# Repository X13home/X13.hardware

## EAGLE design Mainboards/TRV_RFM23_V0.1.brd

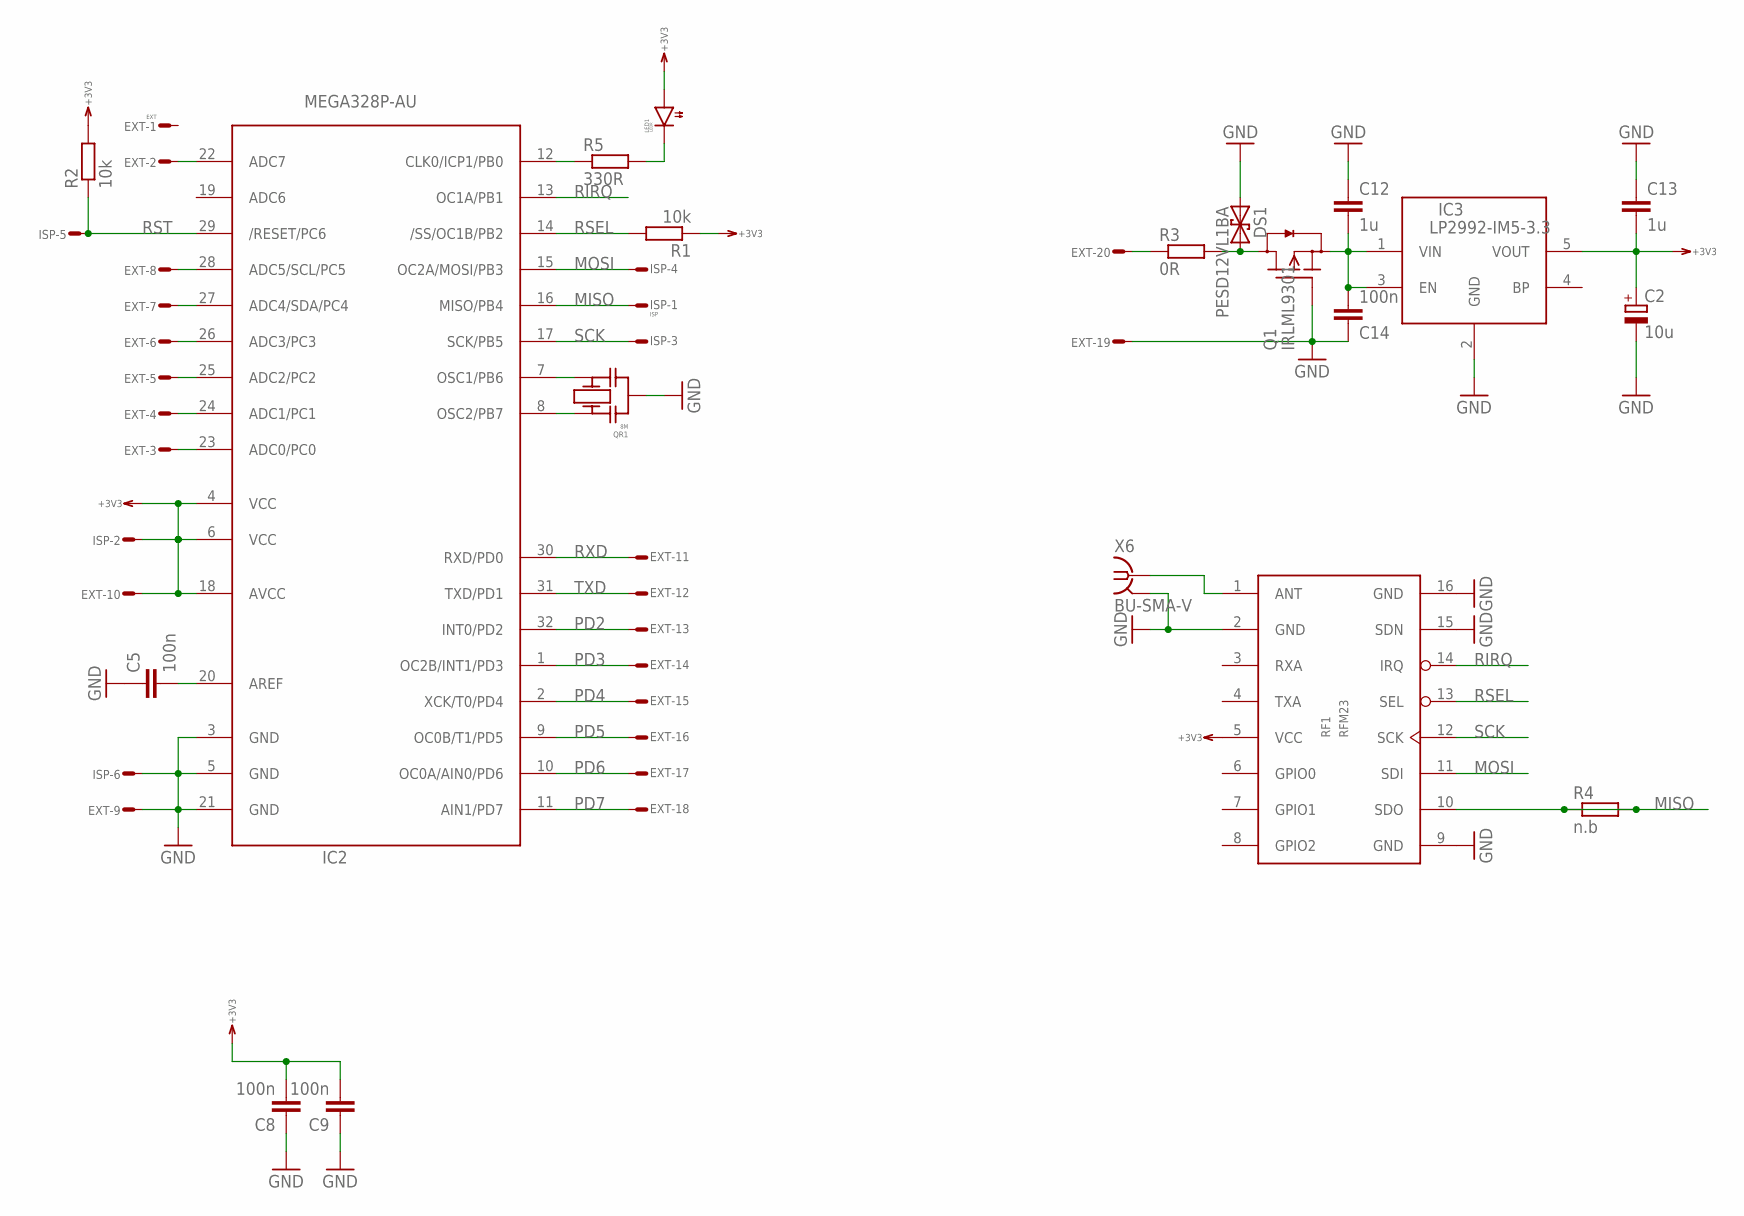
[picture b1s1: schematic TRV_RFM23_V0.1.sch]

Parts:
C2: 10u; SMC_B
C5, C8, C9, C14: 100n; 0603
C12, C13: 1u; 0603
DS1: PESD12VL1BA; SOD323
EXT: EXT; ML20S
IC2: MEGA328P-AU; TQFP32-08
IC3: LP2992-IM5-3.3; SOT23-5
ISP: ISP; ML6S
LED1: LEDR; 0805
Q1: IRLML9301; SOT23
QR1: 8M; CR
R1, R2: 10k; 0603
R3: 0R; 0603
R4: n.b; 0603
R5: 330R; 0603
RF1: RFM23; RFM23B
X6: BU-SMA-V

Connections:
+3V3: C2.+, C8.2, C9.2, C13.2, EXT.10, IC2.4 (VCC), IC2.6 (VCC), IC2.18 (AVCC), IC3.5 (VOUT), ISP.2, LED1.C (A), R1.1, R2.2, RF1.5 (VCC)
GND: C2.-, C5.1, C8.1, C9.1, C12.1, C13.1, C14.1, DS1.A (1), EXT.9, EXT.19, IC2.3 (GND), IC2.5 (GND), IC2.21 (GND), IC3.2 (GND), ISP.6, Q1.1 (G), QR1.M, RF1.2 (GND), RF1.9 (GND), RF1.15 (SDN), RF1.16 (GND), X6.2 (GND), X6.3 (GND), X6.4 (GND), X6.5 (GND)
LED: IC2.12 (CLK0/ICP1/PB0), R5.1
MISO: IC2.16 (MISO/PB4), ISP.1, R4.1, R4.2, RF1.10 (SDO)
MOSI: IC2.15 (OC2A/MOSI/PB3), ISP.4, RF1.11 (SDI)
unnamed: RF1.1 (ANT), X6.1
unnamed: EXT.2, IC2.22 (ADC7)
unnamed: DS1.C (2), Q1.3 (D), R3.2
unnamed: C5.2, IC2.20 (AREF)
unnamed: IC2.8 (OSC2/PB7), QR1.1
unnamed: IC2.7 (OSC1/PB6), QR1.2
unnamed: EXT.20, R3.1
unnamed: C12.2, C14.2, IC3.1 (VIN), IC3.3 (EN), Q1.2 (S)
unnamed: LED1.A (C), R5.2
PC0: EXT.3, IC2.23 (ADC0/PC0)
PC1: EXT.4, IC2.24 (ADC1/PC1)
PC2: EXT.5, IC2.25 (ADC2/PC2)
PC3: EXT.6, IC2.26 (ADC3/PC3)
PC4: EXT.7, IC2.27 (ADC4/SDA/PC4)
PC5: EXT.8, IC2.28 (ADC5/SCL/PC5)
PD2: EXT.13, IC2.32 (INT0/PD2)
PD3: EXT.14, IC2.1 (OC2B/INT1/PD3)
PD4: EXT.15, IC2.2 (XCK/T0/PD4)
PD5: EXT.16, IC2.9 (OC0B/T1/PD5)
PD6: EXT.17, IC2.10 (OC0A/AIN0/PD6)
PD7: EXT.18, IC2.11 (AIN1/PD7)
RIRQ: IC2.13 (OC1A/PB1), RF1.14 (IRQ)
RSEL: IC2.14 (/SS/OC1B/PB2), R1.2, RF1.13 (SEL)
RST: IC2.29 (/RESET/PC6), ISP.5, R2.1
RXD: EXT.11, IC2.30 (RXD/PD0)
SCK: IC2.17 (SCK/PB5), ISP.3, RF1.12 (SCK)
TXD: EXT.12, IC2.31 (TXD/PD1)

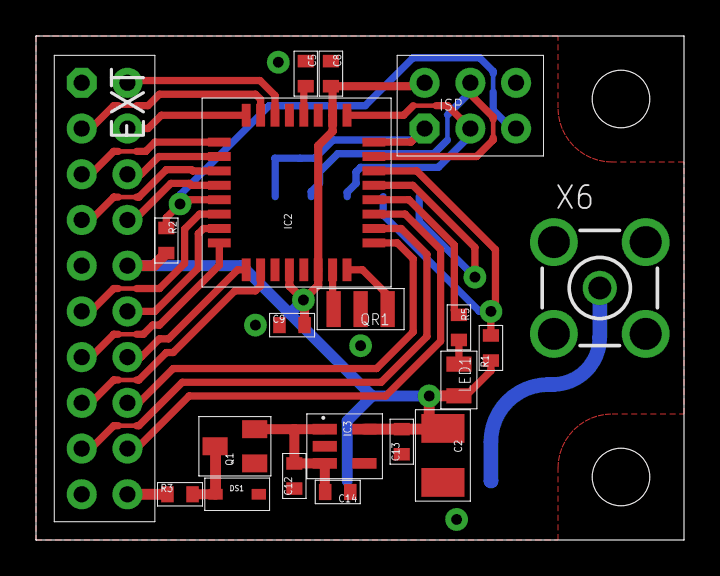
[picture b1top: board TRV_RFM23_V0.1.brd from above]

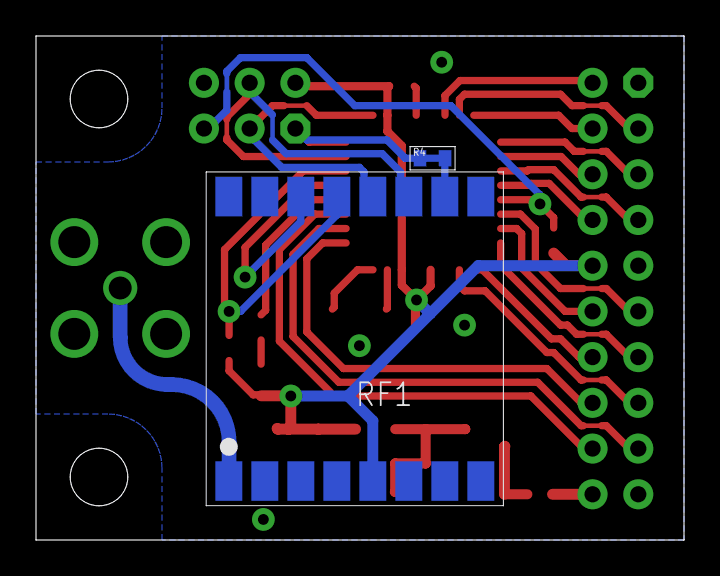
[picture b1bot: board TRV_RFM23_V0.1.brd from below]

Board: 2 copper layers, 36.0 x 28.0 mm, 22 parts (2 on the bottom side), 32 nets.

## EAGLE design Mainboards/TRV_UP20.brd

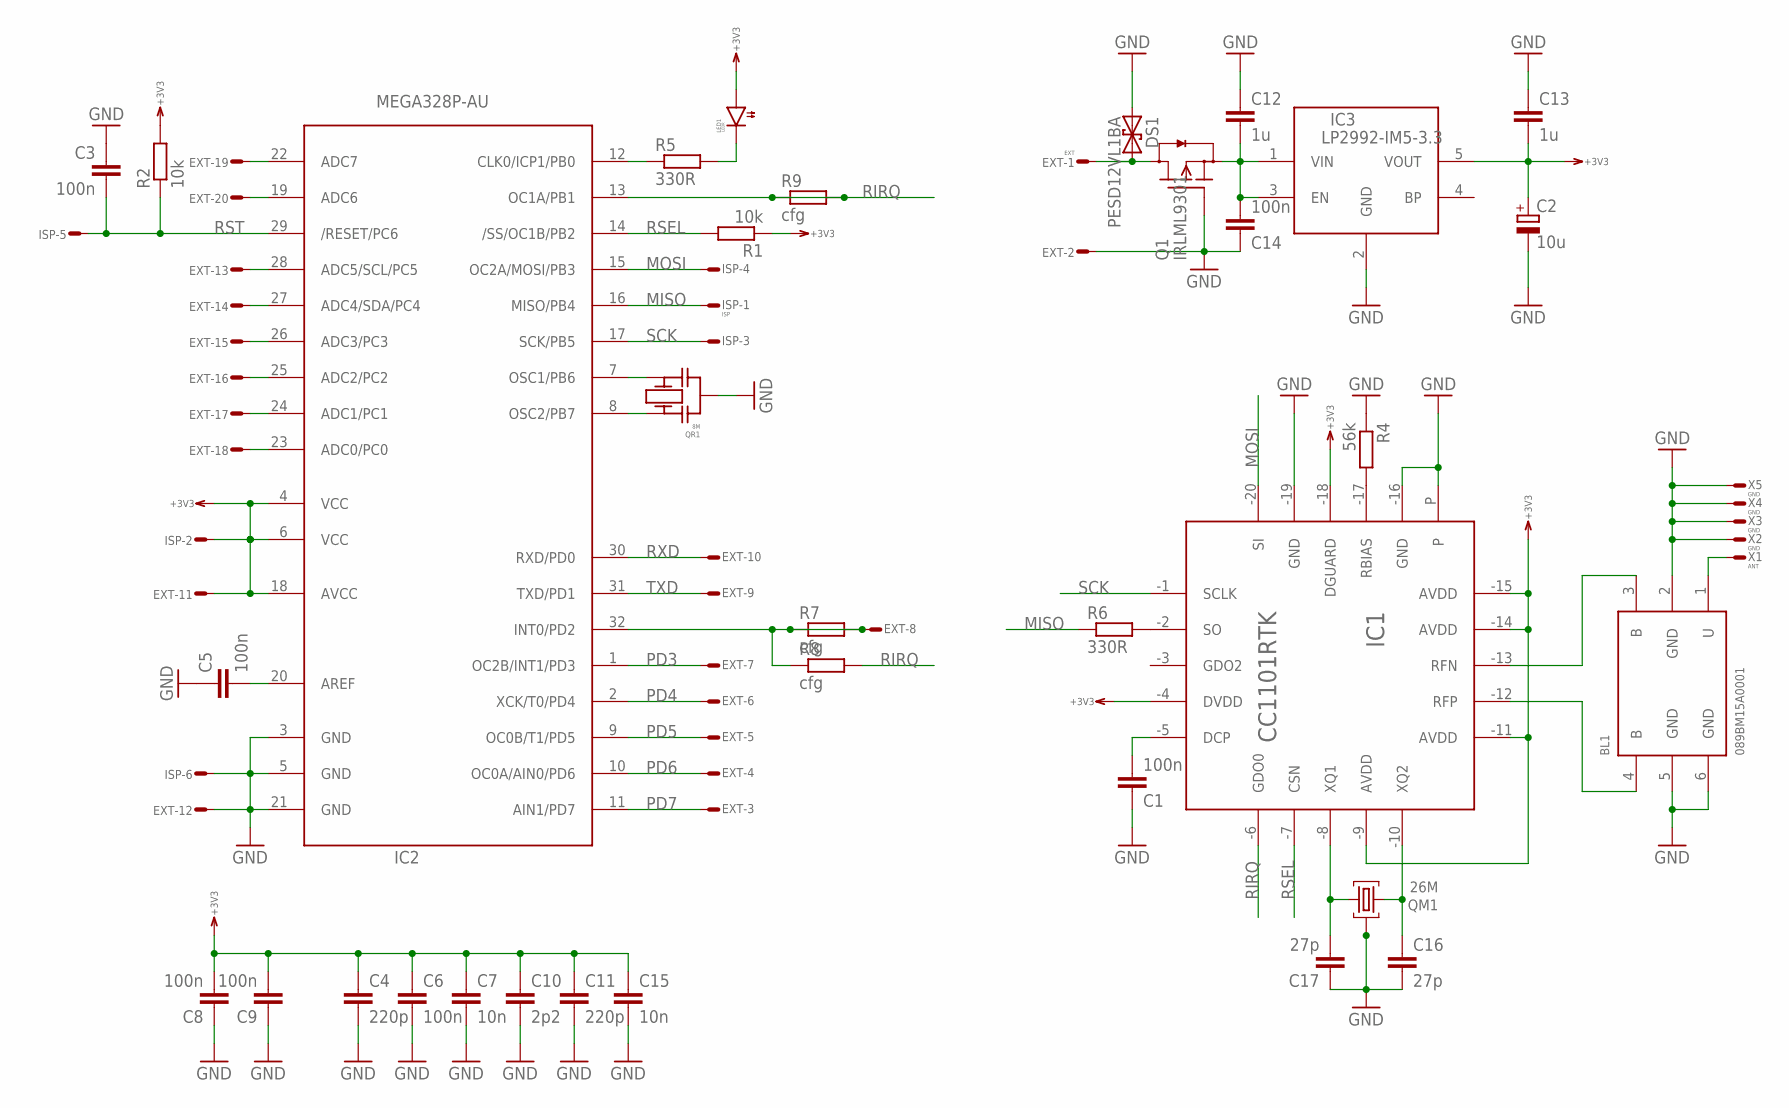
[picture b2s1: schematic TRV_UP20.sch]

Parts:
BL1: 089BM15A0001; BL
C1, C6: 100n; 0402
C2: 10u; SMC_B
C3, C5, C8, C9, C14: 100n; 0603
C4, C11: 220p; 0402
C7, C15: 10n; 0402
C10: 2p2; 0402
C12, C13: 1u; 0603
C16, C17: 27p; 0402
DS1: PESD12VL1BA; SOD323
EXT: EXT; ML20S
IC1: CC1101RTK; VQFN20
IC2: MEGA328P-AU; TQFP32-08
IC3: LP2992-IM5-3.3; SOT23-5
ISP: ISP; ML6S
LED1: LEDR; T1-3/4
Q1: IRLML9301; SOT23
QM1: 26M; SMD_4P_3.2X2.5
QR1: 8M; CSTCE
R1: 10k; 0402
R2: 10k; 0603
R4: 56k; 0402
R5, R6: 330R; 0402
R7, R8, R9: cfg; 0402
X1: ANT; S2.54/1.27
X2, X3, X4, X5: GND; S2.54/1.27

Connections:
+3V3: C2.+, C4.1, C6.1, C7.1, C8.2, C9.2, C10.1, C11.1, C13.2, C15.1, EXT.11, IC1.-4 (DVDD), IC1.-9 (AVDD), IC1.-11 (AVDD), IC1.-14 (AVDD), IC1.-15 (AVDD), IC1.-18 (DGUARD), IC2.4 (VCC), IC2.6 (VCC), IC2.18 (AVCC), IC3.5 (VOUT), ISP.2, LED1.A, R1.1, R2.2
ADC6: EXT.20, IC2.19 (ADC6)
ADC7: EXT.19, IC2.22 (ADC7)
GND: BL1.2 (GND), BL1.5 (GND), BL1.6 (GND), C1.1, C2.-, C3.1, C4.2, C5.1, C6.2, C7.2, C8.1, C9.1, C10.2, C11.2, C12.1, C13.1, C14.1, C15.2, C16.2, C17.1, DS1.A (1), EXT.2, EXT.12, IC1.-16 (GND), IC1.-19 (GND), IC1.P, IC2.3 (GND), IC2.5 (GND), IC2.21 (GND), IC3.2 (GND), ISP.6, Q1.1 (G), QM1.2 (M1), QM1.4 (M2), QR1.G (M), R4.1, X2.1, X3.1, X4.1, X5.1
MISO: IC2.16 (MISO/PB4), ISP.1, R6.1
MOSI: IC1.-20 (SI), IC2.15 (OC2A/MOSI/PB3), ISP.4
unnamed: C1.2, IC1.-5 (DCP)
unnamed: IC1.-17 (RBIAS), R4.2
unnamed: IC1.-2 (SO), R6.2
unnamed: DS1.C (2), EXT.1, Q1.3 (D)
unnamed: C5.2, IC2.20 (AREF)
unnamed: IC2.8 (OSC2/PB7), QR1.A (1)
unnamed: IC2.7 (OSC1/PB6), QR1.B (2)
unnamed: IC2.12 (CLK0/ICP1/PB0), R5.1
unnamed: EXT.8, IC2.32 (INT0/PD2), R7.1, R7.2, R8.1
unnamed: C12.2, C14.2, IC3.1 (VIN), IC3.3 (EN), Q1.2 (S)
unnamed: BL1.3 (B), IC1.-13 (RFN)
unnamed: BL1.4 (B), IC1.-12 (RFP)
unnamed: BL1.1 (U), X1.1
unnamed: C17.2, IC1.-8 (XQ1), QM1.3 (2)
unnamed: C16.1, IC1.-10 (XQ2), QM1.1
unnamed: LED1.C, R5.2
PC0: EXT.18, IC2.23 (ADC0/PC0)
PC1: EXT.17, IC2.24 (ADC1/PC1)
PC2: EXT.16, IC2.25 (ADC2/PC2)
PC3: EXT.15, IC2.26 (ADC3/PC3)
PC4: EXT.14, IC2.27 (ADC4/SDA/PC4)
PC5: EXT.13, IC2.28 (ADC5/SCL/PC5)
PD3: EXT.7, IC2.1 (OC2B/INT1/PD3)
PD4: EXT.6, IC2.2 (XCK/T0/PD4)
PD5: EXT.5, IC2.9 (OC0B/T1/PD5)
PD6: EXT.4, IC2.10 (OC0A/AIN0/PD6)
PD7: EXT.3, IC2.11 (AIN1/PD7)
RIRQ: IC1.-6 (GDO0), IC2.13 (OC1A/PB1), R8.2, R9.1, R9.2
RSEL: IC1.-7 (CSN), IC2.14 (/SS/OC1B/PB2), R1.2
RST: C3.2, IC2.29 (/RESET/PC6), ISP.5, R2.1
RXD: EXT.10, IC2.30 (RXD/PD0)
SCK: IC1.-1 (SCLK), IC2.17 (SCK/PB5), ISP.3
TXD: EXT.9, IC2.31 (TXD/PD1)

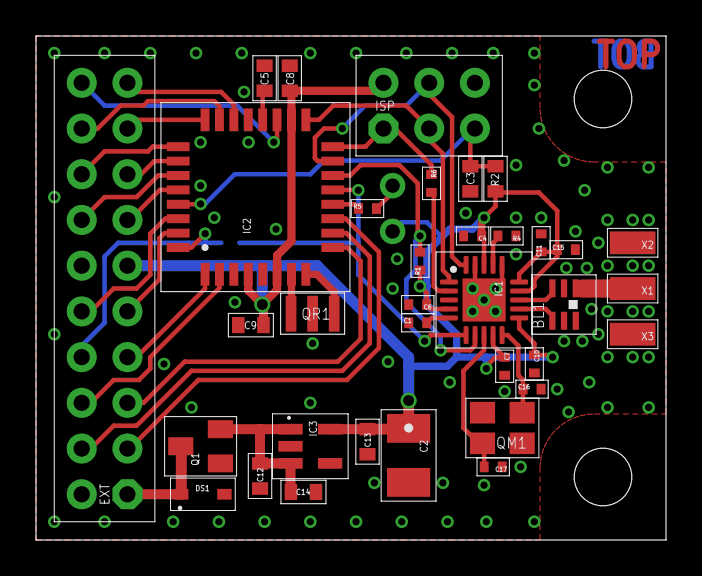
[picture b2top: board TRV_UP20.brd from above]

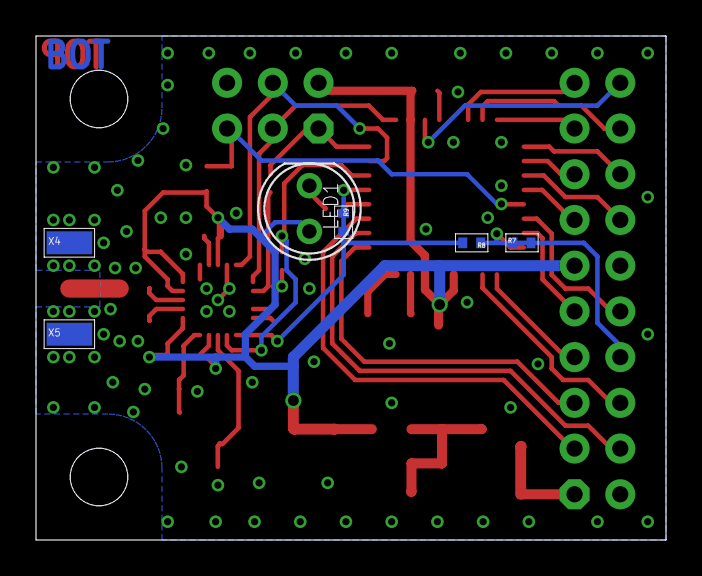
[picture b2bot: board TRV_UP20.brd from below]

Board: 2 copper layers, 35.0 x 28.0 mm, 41 parts (6 on the bottom side), 39 nets.

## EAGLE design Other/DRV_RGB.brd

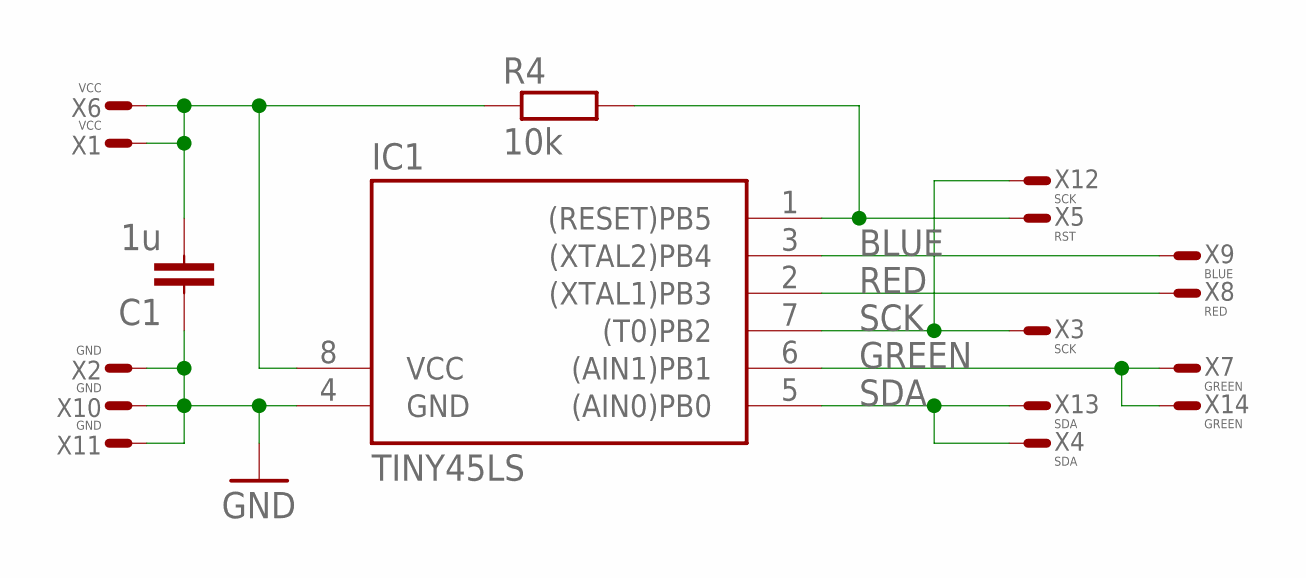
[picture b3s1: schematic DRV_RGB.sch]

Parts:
C1: 1u; 0603
IC1: TINY45LS; SOIC8
R4: 10k; 0603
X1, X6: VCC; T1.6/0.9
X2, X10, X11: GND; T1.6/0.9
X3, X12: SCK; T1.6/0.9
X4, X13: SDA; T1.6/0.9
X5: RST; T1.6/0.9
X7, X14: GREEN; T1.6/0.9
X8: RED; T1.6/0.9
X9: BLUE; T1.6/0.9

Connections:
BLUE: IC1.3 ((XTAL2)PB4), X9.1
GND: C1.1, IC1.4 (GND), X2.1, X10.1, X11.1
GREEN: IC1.6 ((AIN1)PB1), X7.1, X14.1
unnamed: C1.2, IC1.8 (VCC), R4.1, X1.1, X6.1
unnamed: IC1.1 ((RESET)PB5), R4.2, X5.1
RED: IC1.2 ((XTAL1)PB3), X8.1
SCK: IC1.7 ((T0)PB2), X3.1, X12.1
SDA: IC1.5 ((AIN0)PB0), X4.1, X13.1

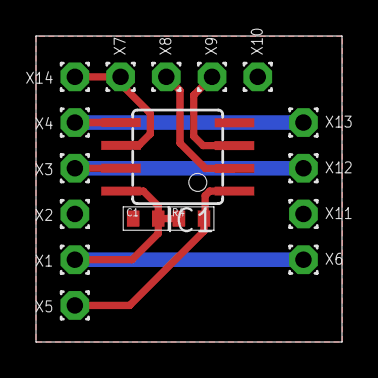
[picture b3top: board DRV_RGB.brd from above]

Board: 2 copper layers, 17.0 x 17.0 mm, 17 parts (0 on the bottom side), 8 nets.

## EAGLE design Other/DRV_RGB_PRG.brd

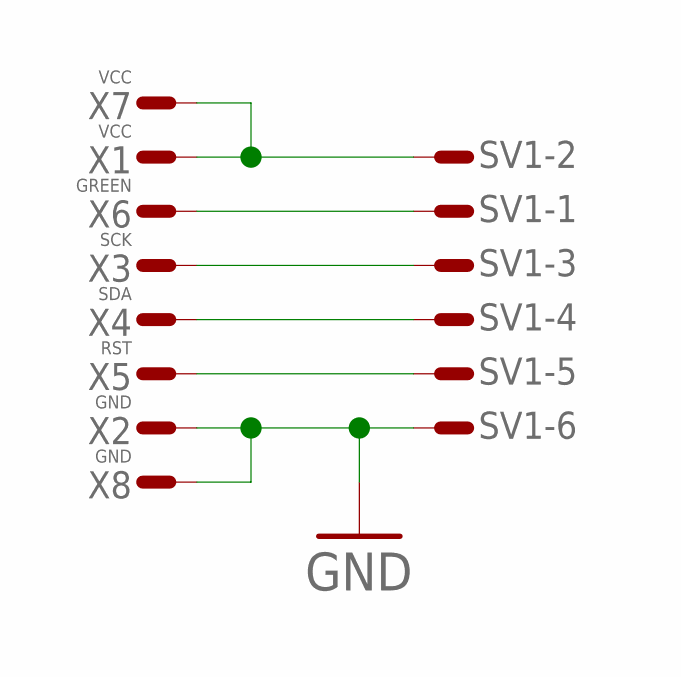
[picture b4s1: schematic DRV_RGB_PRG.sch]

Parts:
SV1: ML6ES; ML6S
X1, X7: VCC; T1.6/0.9
X2, X8: GND; T1.6/0.9
X3: SCK; T1.6/0.9
X4: SDA; T1.6/0.9
X5: RST; T1.6/0.9
X6: GREEN; T1.6/0.9

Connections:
GND: SV1.6, X2.1, X8.1
GREEN: SV1.1, X6.1
unnamed: SV1.5, X5.1
SCK: SV1.3, X3.1
SDA: SV1.4, X4.1
VCC: SV1.2, X1.1, X7.1

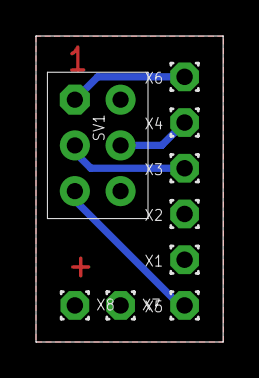
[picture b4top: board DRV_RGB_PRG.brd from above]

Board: 2 copper layers, 10.4 x 17.0 mm, 9 parts (0 on the bottom side), 6 nets.

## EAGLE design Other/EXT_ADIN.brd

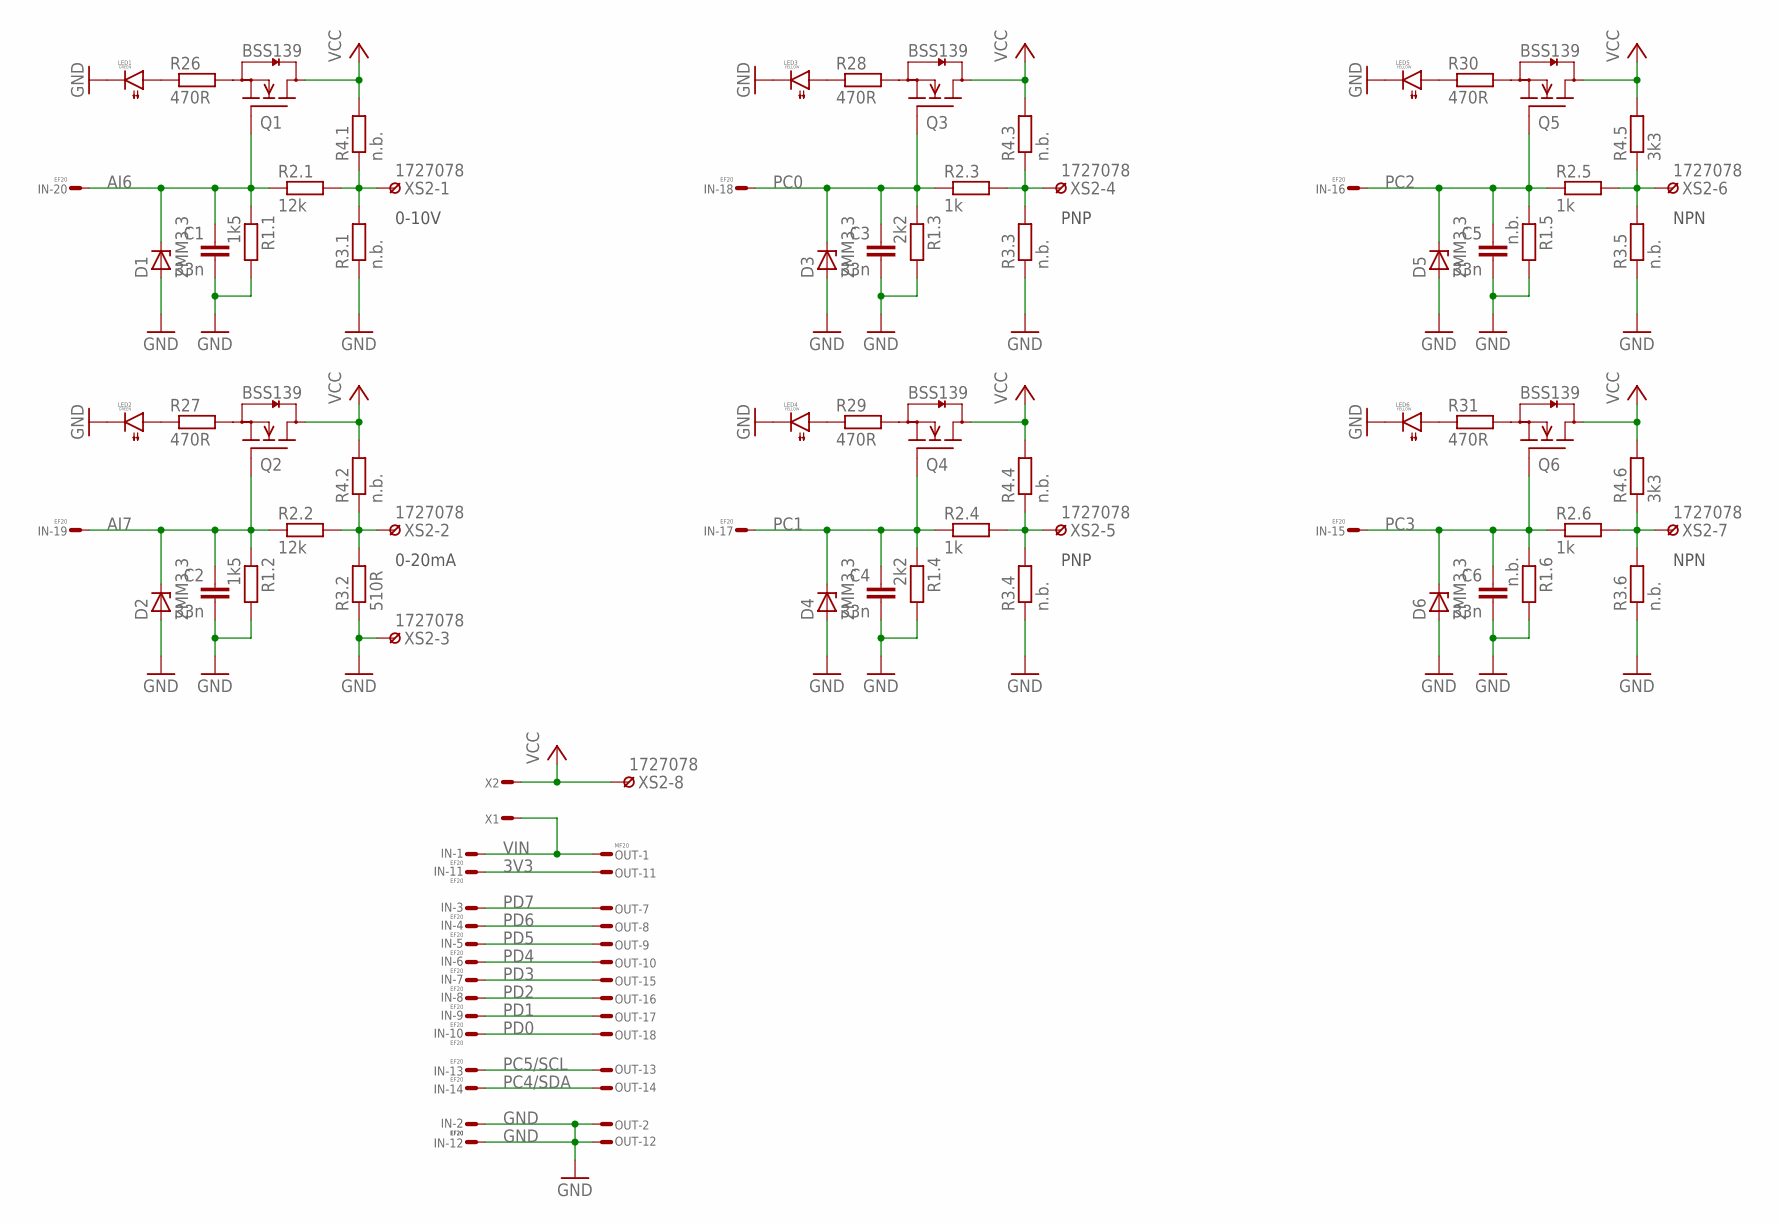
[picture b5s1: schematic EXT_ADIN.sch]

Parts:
C1, C2, C3, C4, C5, C6: 33n; 1206
D1, D2, D3, D4, D5, D6: ZMM3,3; SOD80
IN: EF20; FE10-2WSS
LED1, LED2: GREEN; 1206
LED3, LED4, LED5, LED6: YELLOW; 1206
OUT: MF20; ML20LS
Q1, Q2, Q3, Q4, Q5, Q6: BSS139; SOT23
R1.1, R1.2: 1k5; 1206
R1.3, R1.4: 2k2; 1206
R1.5, R1.6, R3.1, R3.3, R3.4, R3.5, R3.6, R4.1, R4.2, R4.3, R4.4: n.b.; 1206
R2.1, R2.2: 12k; 1206
R2.3, R2.4, R2.5, R2.6: 1k; 1206
R3.2: 510R; 1206
R4.5, R4.6: 3k3; 1206
R26, R27, R28, R29, R30, R31: 470R; 1206
X1, X2: WIREPADT1.6/0.9; T1.6/0.9
XS2: 1727078

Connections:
3V3: IN.P$11, OUT.P$11
AI6: C1.1, D1.C, IN.P$20, Q1.1 (G), R1.1.1, R2.1.1
AI7: C2.1, D2.C, IN.P$19, Q2.1 (G), R1.2.1, R2.2.1
GND: C1.2, C2.2, C3.2, C4.2, C5.2, C6.2, D1.A, D2.A, D3.A, D4.A, D5.A, D6.A, IN.P$2, IN.P$12, LED1.2 (C), LED2.2 (C), LED3.2 (C), LED4.2 (C), LED5.2 (C), LED6.2 (C), OUT.P$2, OUT.P$12, R1.1.2, R1.2.2, R1.3.2, R1.4.2, R1.5.2, R1.6.2, R3.1.1, R3.2.1, R3.3.1, R3.4.1, R3.5.1, R3.6.1, XS2.P$3
unnamed: R2.2.2, R3.2.2, R4.2.1, XS2.P$2
unnamed: R2.3.2, R3.3.2, R4.3.1, XS2.P$4
unnamed: R2.1.2, R3.1.2, R4.1.1, XS2.P$1
unnamed: R2.4.2, R3.4.2, R4.4.1, XS2.P$5
unnamed: R2.5.2, R3.5.2, R4.5.1, XS2.P$6
unnamed: R2.6.2, R3.6.2, R4.6.1, XS2.P$7
unnamed: LED1.1 (A), R26.1
unnamed: Q1.2 (S), R26.2
unnamed: LED2.1 (A), R27.1
unnamed: Q2.2 (S), R27.2
unnamed: LED3.1 (A), R28.1
unnamed: Q3.2 (S), R28.2
unnamed: LED4.1 (A), R29.1
unnamed: Q4.2 (S), R29.2
unnamed: LED5.1 (A), R30.1
unnamed: Q5.2 (S), R30.2
unnamed: LED6.1 (A), R31.1
unnamed: Q6.2 (S), R31.2
PC0: C3.1, D3.C, IN.P$18, Q3.1 (G), R1.3.1, R2.3.1
PC1: C4.1, D4.C, IN.P$17, Q4.1 (G), R1.4.1, R2.4.1
PC2: C5.1, D5.C, IN.P$16, Q5.1 (G), R1.5.1, R2.5.1
PC3: C6.1, D6.C, IN.P$15, Q6.1 (G), R1.6.1, R2.6.1
PC4/SDA: IN.P$14, OUT.P$14
PC5/SCL: IN.P$13, OUT.P$13
PD0: IN.P$10, OUT.P$18
PD1: IN.P$9, OUT.P$17
PD2: IN.P$8, OUT.P$16
PD3: IN.P$7, OUT.P$15
PD4: IN.P$6, OUT.P$10
PD5: IN.P$5, OUT.P$9
PD6: IN.P$4, OUT.P$8
PD7: IN.P$3, OUT.P$7
VCC: Q1.3 (D), Q2.3 (D), Q3.3 (D), Q4.3 (D), Q5.3 (D), Q6.3 (D), R4.1.2, R4.2.2, R4.3.2, R4.4.2, R4.5.2, R4.6.2, X2.1, XS2.P$8
VIN: IN.P$1, OUT.P$1, X1.1

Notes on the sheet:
0-10V
0-20mA
PNP
NPN

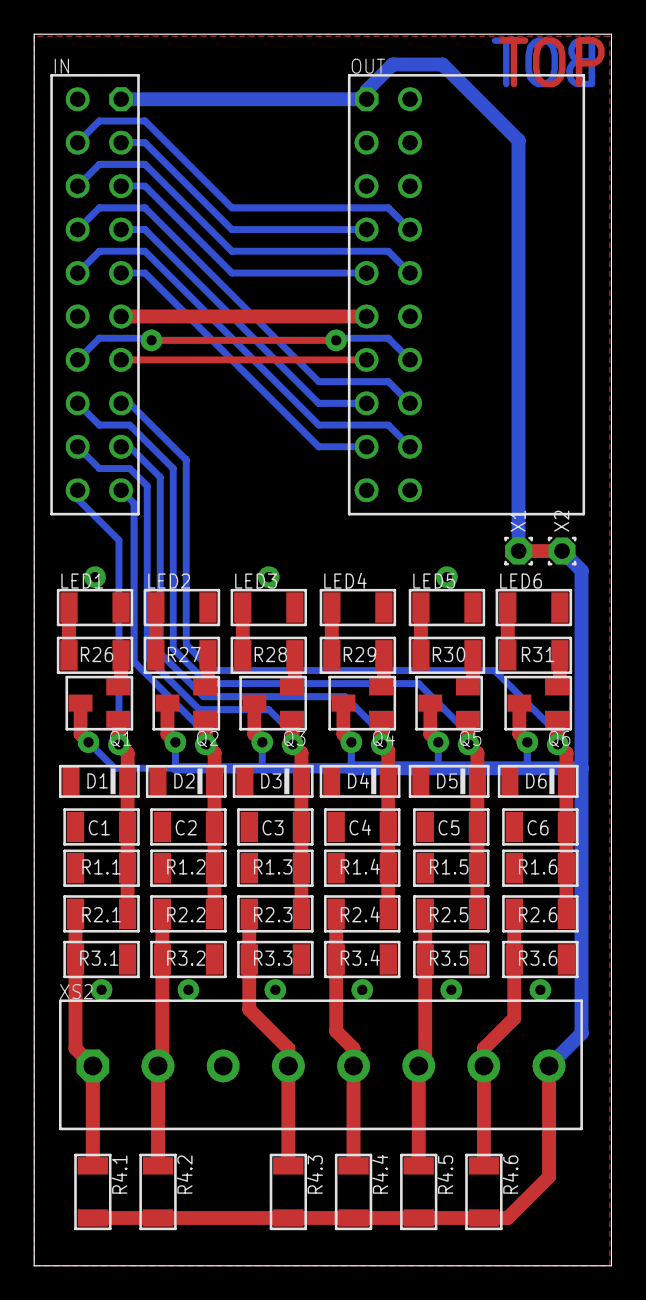
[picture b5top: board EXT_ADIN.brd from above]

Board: 2 copper layers, 33.8 x 72.0 mm, 59 parts (0 on the bottom side), 38 nets.
